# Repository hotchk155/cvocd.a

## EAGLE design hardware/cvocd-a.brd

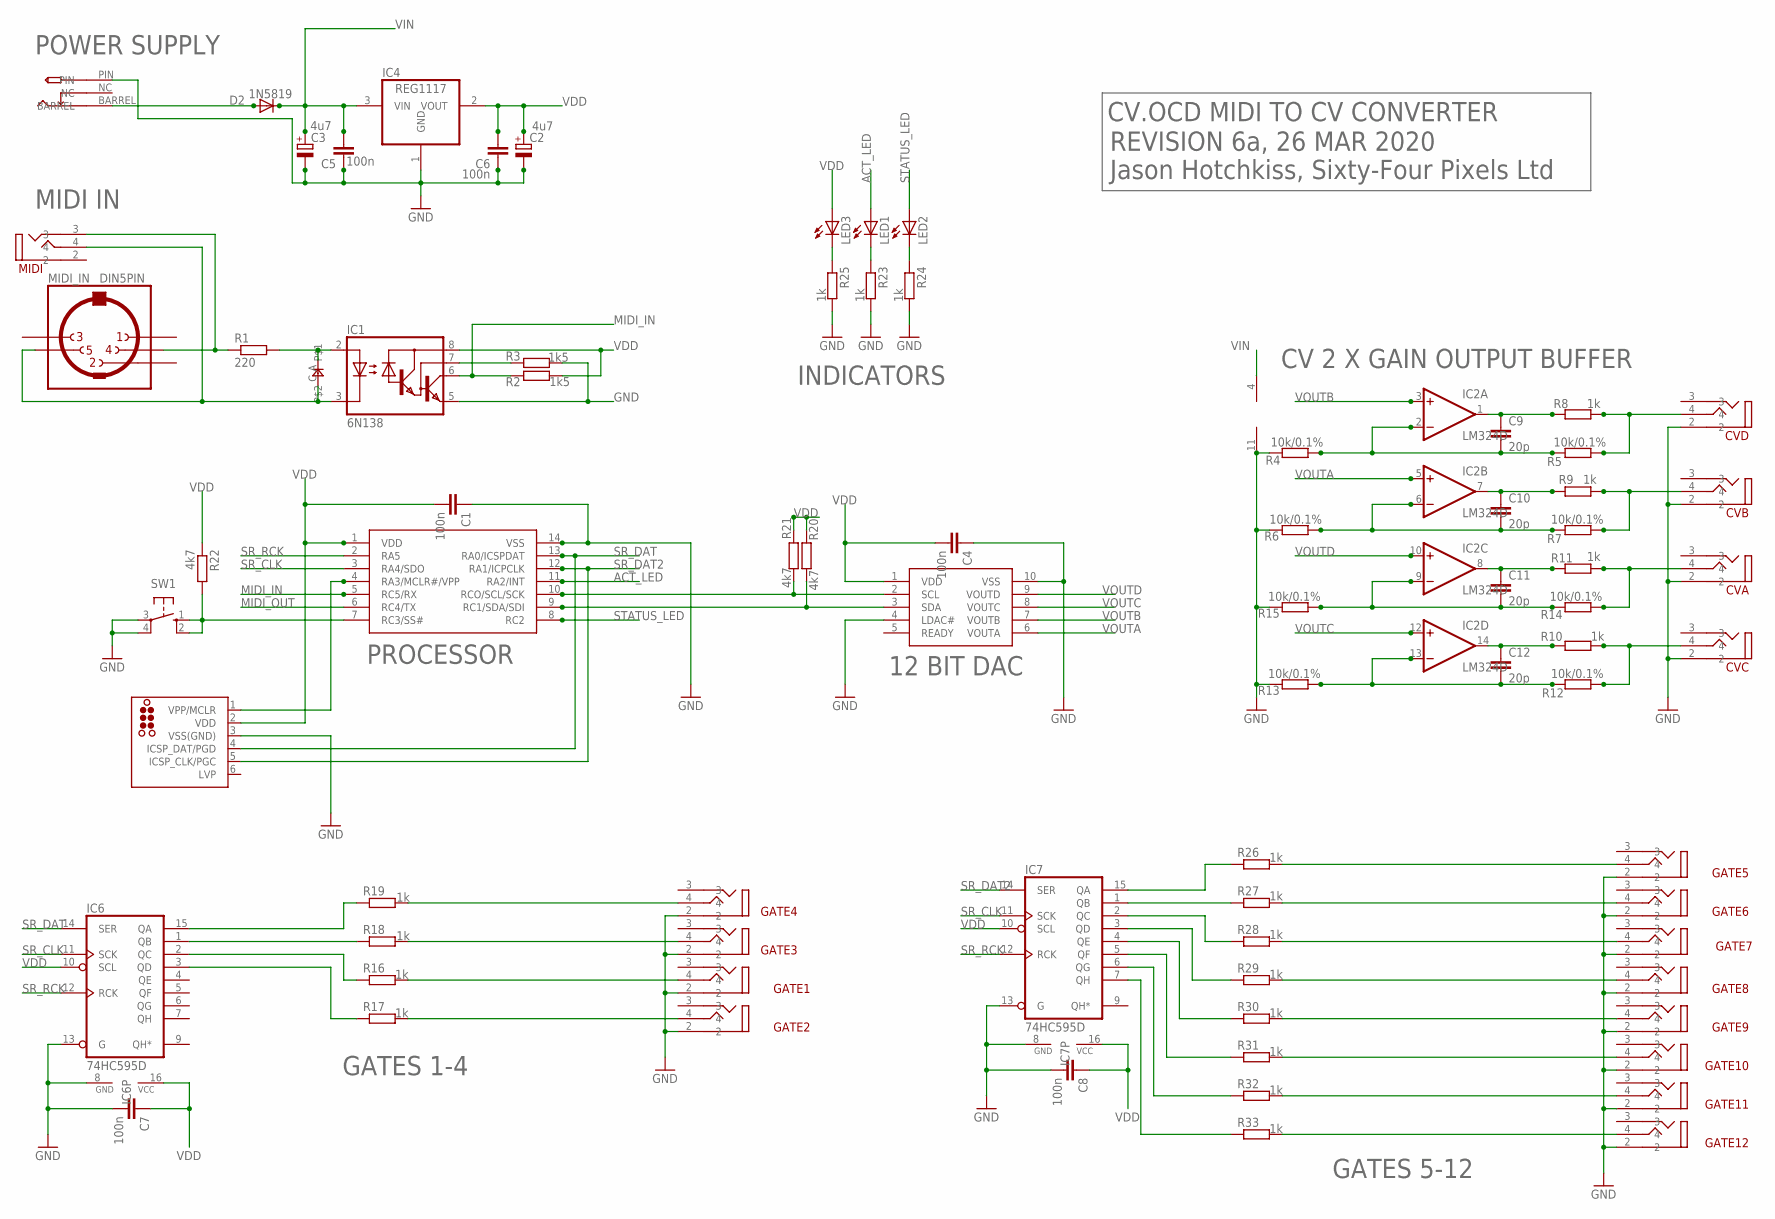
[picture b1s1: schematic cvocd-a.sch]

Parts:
C1, C4, C5, C6, C7, C8: 100n; C0805
C2, C3: 4u7; PANASONIC_C
C9, C10, C11, C12: 20p; C0805
CVA: VERTICAL_3_5MM_SOCKET
CVB: VERTICAL_3_5MM_SOCKET
CVC: VERTICAL_3_5MM_SOCKET
CVD: VERTICAL_3_5MM_SOCKET
D1: 0805DIODE
D2: 1N5819; SOD123
GATE1, GATE2, GATE3, GATE4, GATE5, GATE6, GATE7, GATE8, GATE9, GATE10, GATE11, GATE12: VERTICAL_3_5MM_SOCKET
IC1: 6N138; DIL08
IC2: LM324D; SO14
IC3: MCP4728_QUAD_DAC; MSOP10
IC4: REG1117; SOT223
IC5: PIC16F1825SO14; SO14
IC6, IC7: 74HC595D; SO16
ICSP: TC2030-MCP-NL
LED1, LED2, LED3: LED3MM
MIDI: VERTICAL_3_5MM_SOCKET
MIDI_IN: DIN5PIN; EDGEDIN
R1: 220; R0805
R2, R3: 1k5; R0805
R4, R5, R6, R7, R12, R13, R14, R15: 10k/0.1%; R0805
R8, R9, R10, R11, R16, R17, R18, R19, R23, R24, R25, R26, R27, R28, R29, R30, R31, R32, R33: 1k; R0805
R20, R21, R22: 4k7; R0805
SW1: 10-XX; B3F-10XX
U$2: PWR_SOCKET_2_1MM

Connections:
ACT_LED: IC5.11 (RA2/INT), LED1.A
GND: C1.1, C2.-, C3.-, C4.1, C5.1, C6.1, C7.2, C8.2, CVA.2, CVB.2, CVC.2, CVD.2, GATE1.2, GATE2.2, GATE3.2, GATE4.2, GATE5.2, GATE6.2, GATE7.2, GATE8.2, GATE9.2, GATE10.2, GATE11.2, GATE12.2, IC1.5 (GND), IC2.11 (V-), IC3.4 (LDAC#), IC3.10 (VSS), IC4.1 (GND), IC5.14 (VSS), IC6.8 (GND), IC6.13 (G), IC7.8 (GND), IC7.13 (G), ICSP.3 (VSS(GND)), R3.2, R4.1, R6.1, R13.1, R15.1, R23.2, R24.2, R25.2, SW1.3, SW1.4 (P1), U$2.PIN
MIDI_IN: IC1.6 (VO), IC5.5 (RC5/RX), R2.1
MIDI_OUT: IC5.6 (RC4/TX)
unnamed: GATE4.4, R19.2
unnamed: C9.1, IC2.1 (OUT), R8.1
unnamed: C10.1, IC2.7 (OUT), R9.1
unnamed: C11.1, IC2.8 (OUT), R11.1
unnamed: C12.1, IC2.14 (OUT), R10.1
unnamed: GATE3.4, R18.2
unnamed: GATE1.4, R16.2
unnamed: GATE2.4, R17.2
unnamed: IC5.7 (RC3/SS#), R22.2, SW1.1 (S), SW1.2 (S1)
unnamed: C9.2, IC2.2 (-IN), R4.2, R5.1
unnamed: C11.2, IC2.9 (-IN), R14.1, R15.2
unnamed: IC6.15 (QA), R19.1
unnamed: IC6.1 (QB), R18.1
unnamed: C12.2, IC2.13 (-IN), R12.1, R13.2
unnamed: IC6.3 (QD), R17.1
unnamed: IC6.2 (QC), R16.1
unnamed: CVD.4, R5.2, R8.2
unnamed: CVB.4, R7.2, R9.2
unnamed: GATE5.4, R26.2
unnamed: IC3.2 (SCL), IC5.10 (RCO/SCL/SCK), R21.2
unnamed: IC3.3 (SDA), IC5.9 (RC1/SDA/SDI), R20.2
unnamed: GATE6.4, R27.2
unnamed: GATE7.4, R28.2
unnamed: C10.2, IC2.6 (-IN), R6.2, R7.1
unnamed: MIDI.3, MIDI_IN.4, R1.1
unnamed: D1.A, IC1.2 (A), R1.2
unnamed: D1.C, IC1.3 (C), MIDI.4, MIDI_IN.5
unnamed: GATE8.4, R29.2
unnamed: GATE9.4, R30.2
unnamed: IC5.4 (RA3/MCLR#/VPP), ICSP.1 (VPP/MCLR)
unnamed: LED3.K (C), R25.1
unnamed: LED1.K (C), R23.1
unnamed: LED2.K (C), R24.1
unnamed: CVA.4, R11.2, R14.2
unnamed: GATE10.4, R31.2
unnamed: D2.A, U$2.BARREL
unnamed: GATE11.4, R32.2
unnamed: IC1.7 (VB), R3.1
unnamed: IC7.15 (QA), R26.1
unnamed: CVC.4, R10.2, R12.2
unnamed: IC7.1 (QB), R27.1
unnamed: IC7.3 (QD), R29.1
unnamed: IC7.2 (QC), R28.1
unnamed: IC7.5 (QF), R31.1
unnamed: IC7.6 (QG), R32.1
unnamed: IC7.4 (QE), R30.1
unnamed: GATE12.4, R33.2
unnamed: IC7.7 (QH), R33.1
SR_CLK: IC5.3 (RA4/SDO), IC6.11 (SCK), IC7.11 (SCK)
SR_DAT: IC5.13 (RA0/ICSPDAT), IC6.14 (SER), ICSP.4 (ICSP_DAT/PGD)
SR_DAT2: IC5.12 (RA1/ICPCLK), IC7.14 (SER), ICSP.5 (ICSP_CLK/PGC)
SR_RCK: IC5.2 (RA5), IC6.12 (RCK), IC7.12 (RCK)
STATUS_LED: IC5.8 (RC2), LED2.A
VDD: C1.2, C2.+, C4.2, C6.2, C7.1, C8.1, IC1.8 (VCC), IC3.1 (VDD), IC4.2 (VOUT), IC5.1 (VDD), IC6.10 (SCL), IC6.16 (VCC), IC7.10 (SCL), IC7.16 (VCC), ICSP.2 (VDD), LED3.A, R2.2, R20.1, R21.1, R22.1
VIN: C3.+, C5.2, D2.C, IC2.4 (V+), IC4.3 (VIN)
VOUTA: IC2.5 (+IN), IC3.6 (VOUTA)
VOUTB: IC2.3 (+IN), IC3.7 (VOUTB)
VOUTC: IC2.12 (+IN), IC3.8 (VOUTC)
VOUTD: IC2.10 (+IN), IC3.9 (VOUTD)

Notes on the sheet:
CV.OCD MIDI TO CV CONVERTER
REVISION 6a, 26 MAR 2020
Jason Hotchkiss, Sixty-Four Pixels Ltd
POWER SUPPLY
MIDI IN
PROCESSOR
12 BIT DAC
CV 2 X GAIN OUTPUT BUFFER
GATES 1-4
GATES 5-12
INDICATORS

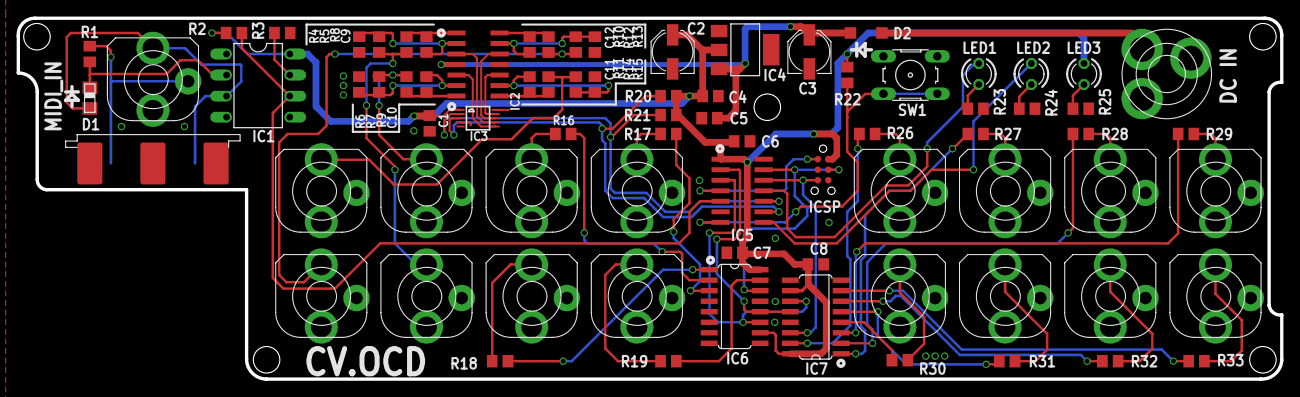
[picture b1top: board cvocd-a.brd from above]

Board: 2 copper layers, 152.5 x 43.6 mm, 78 parts (0 on the bottom side), 62 nets.

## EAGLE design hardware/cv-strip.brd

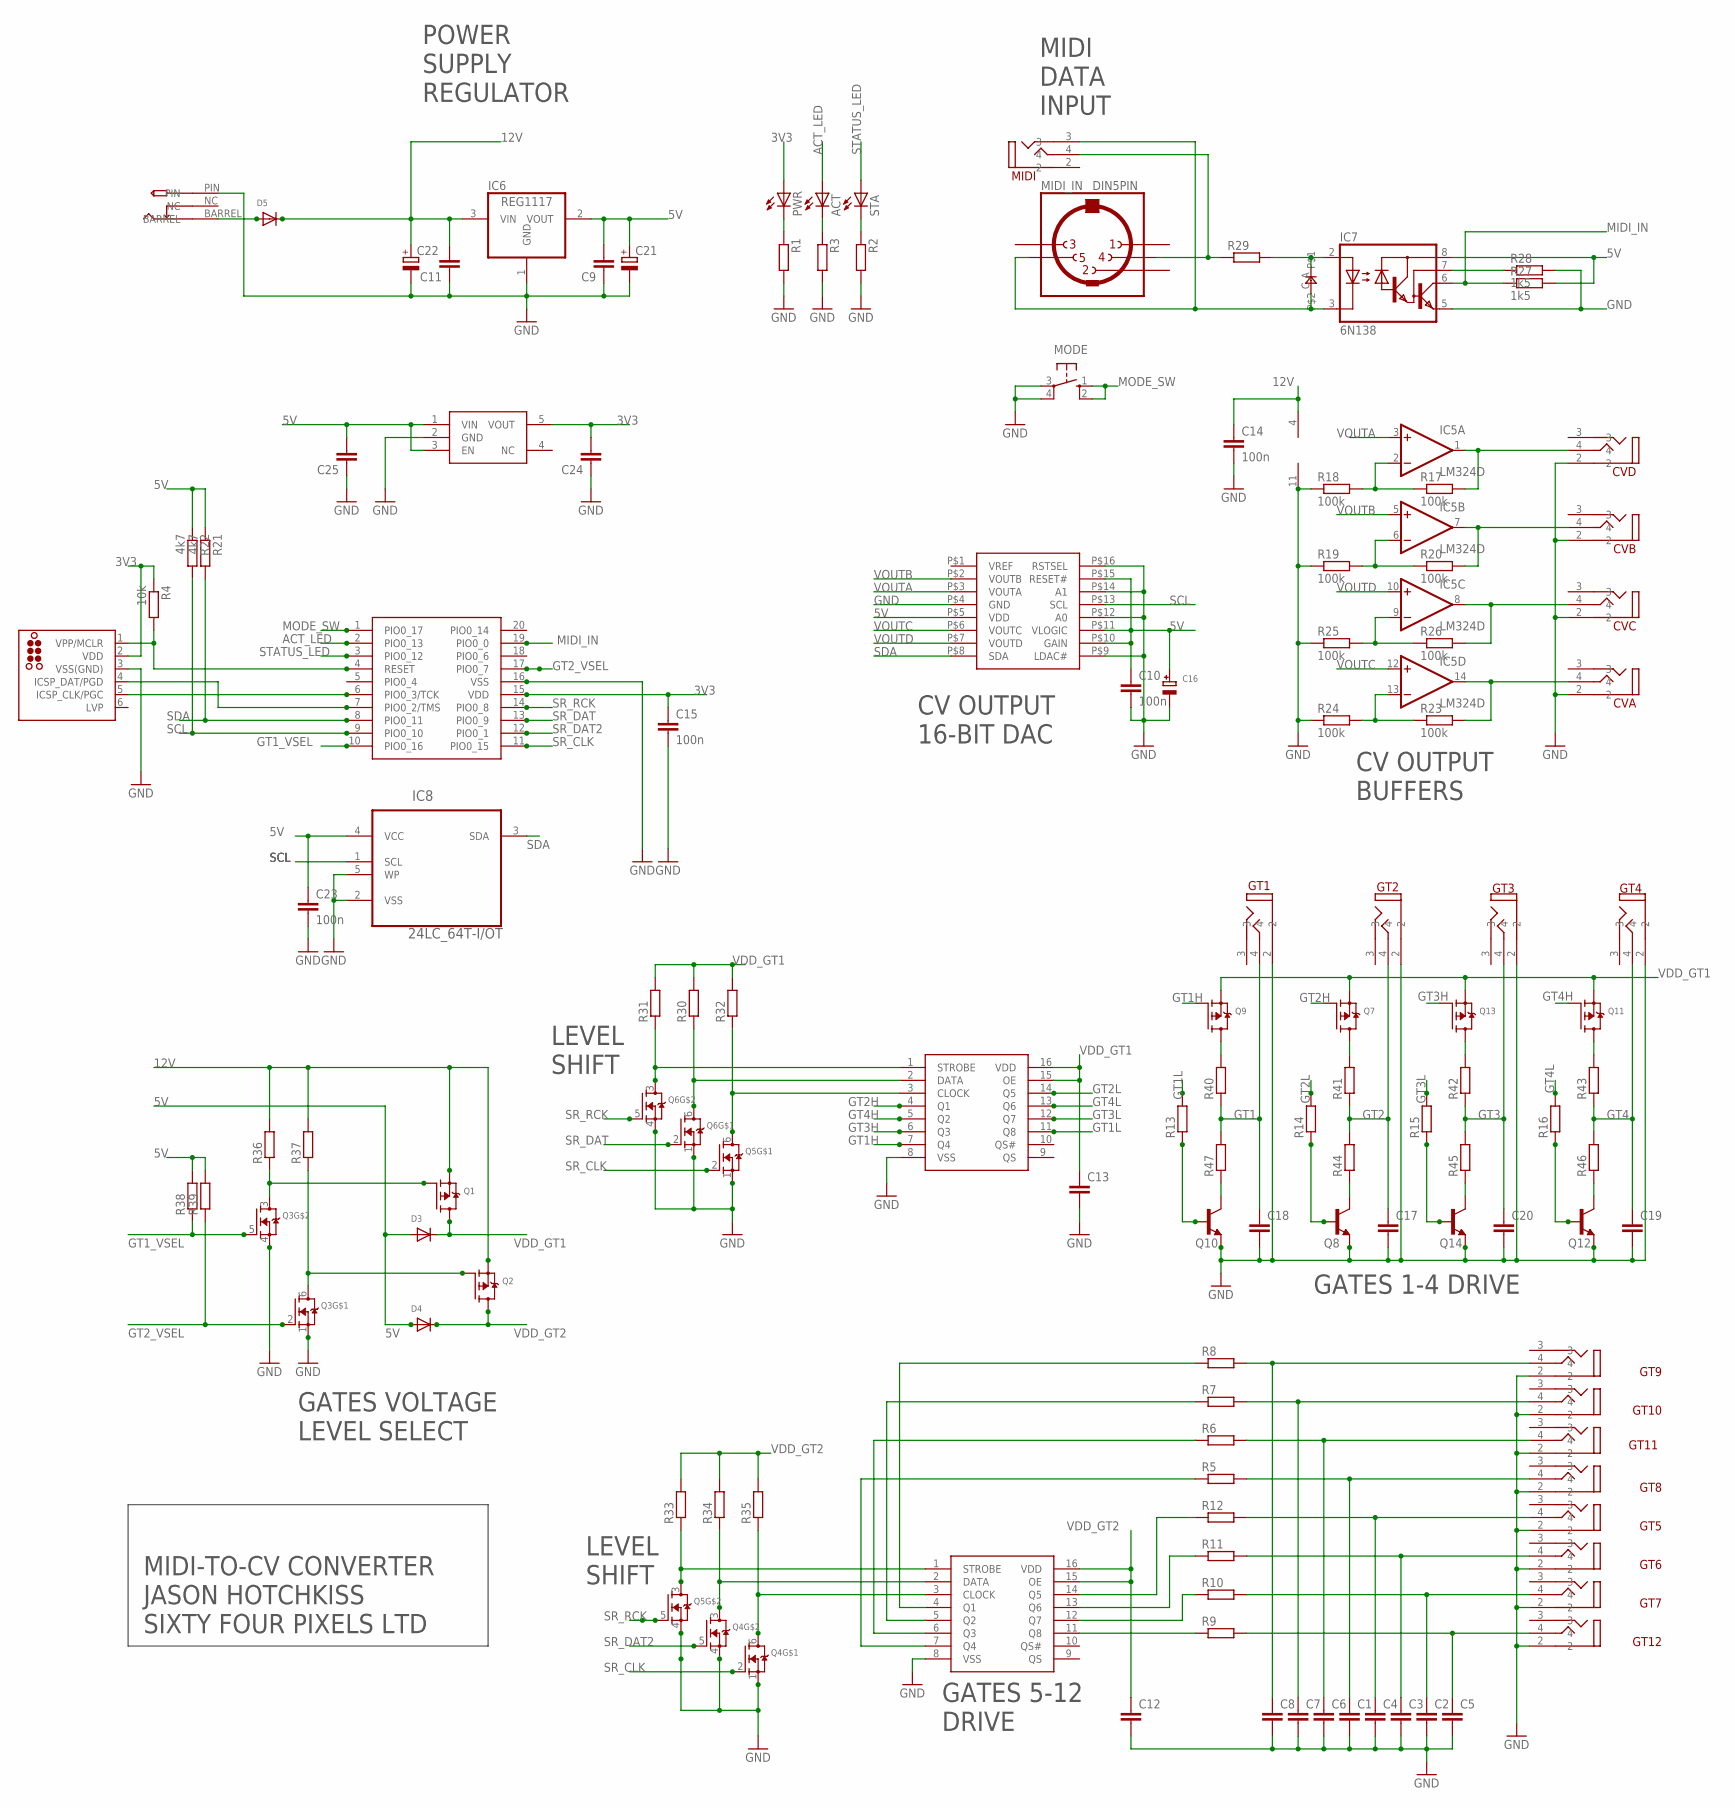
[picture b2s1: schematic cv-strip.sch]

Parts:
ACT: LED3MM
C1, C2, C3, C4, C5, C6, C7, C8, C9, C11, C12, C13, C17, C18, C19, C20, C24, C25: C-EUC0805; C0805
C10, C14, C15, C23: 100n; C0805
C16: CAP_TANTALUMA/3216_REFLOW; EIA3216-18/A-R
C21, C22: CPOL-EUE2.5-5; E2,5-5
CVA: VERTICAL_3_5MM_SOCKET
CVB: VERTICAL_3_5MM_SOCKET
CVC: VERTICAL_3_5MM_SOCKET
CVD: VERTICAL_3_5MM_SOCKET
D1: 0805DIODE
D3, D4, D5: DIODESOD-123; SOD-123
GT1, GT2, GT3, GT4, GT5, GT6, GT7, GT8, GT9, GT10, GT11, GT12: VERTICAL_3_5MM_SOCKET
IC1: LPC812; TSSOP20
IC2: AD5696R; SSOP16
IC3, IC4: MC14094B; SO16
IC5: LM324D; SO14
IC6: REG1117; SOT223
IC7: 6N138; DIL08
IC8: 24LC_64T-I/OT; SOT95P290X145-5N
IC9: MIC5504-2.8YM5-TR; SOT23-5
ICSP: TC2030-MCP-NL
MIDI: VERTICAL_3_5MM_SOCKET
MIDI_IN: DIN5PIN; EDGEDIN
MODE: 10-XX; B3F-10XX
PWR: LED3MM
Q1, Q2, Q7, Q9, Q11, Q13: MOSFET-P; SOT23-R
Q3, Q4, Q5, Q6: MOSFET-N_DUAL; SOT363
Q8, Q10, Q12, Q14: MMBT3904LT1-NPN-SOT23-BEC; SOT23-BEC
R1, R2, R3, R5, R6, R7, R8, R9, R10, R11, R12, R13, R14, R15, R16, R29, R30, R31, R32, R33, R34, R35, R36, R37, R38, R39, R40, R41, R42, R43, R44, R45, R46, R47: R-EU_R0805; R0805
R4: 10k; R0805
R17, R18, R19, R20, R23, R24, R25, R26: 100k; R0805
R21, R22: 4k7; R0805
R27, R28: 1k5; R0805
STA: LED3MM
U$2: PWR_SOCKET_2_1MM

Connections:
3V3: C15.1, C24.2, IC1.15 (VDD), IC9.5 (VOUT), ICSP.2 (VDD), PWR.A, R4.1
5V: C9.2, C10.1, C16.+, C21.+, C23.1, C25.2, D3.A, D4.A, IC2.P$5 (VDD), IC2.P$10 (GAIN), IC2.P$11 (VLOGIC), IC2.P$15 (RESET#), IC6.2 (VOUT), IC7.8 (VCC), IC8.4 (VCC), IC9.1 (VIN), IC9.3 (EN), R21.1, R22.1, R27.2, R38.2, R39.2
12V: C11.2, C14.1, C22.+, D5.C, IC5.4 (V+), IC6.3 (VIN), Q1.2 (S), Q2.2 (S), R36.2, R37.2
ACT_LED: ACT.A, IC1.2 (PIO0_13)
GND: C1.2, C2.2, C3.2, C4.2, C5.2, C6.2, C7.2, C8.2, C9.1, C10.2, C11.1, C12.2, C13.2, C14.2, C15.2, C16.-, C17.2, C18.2, C19.2, C20.2, C21.-, C22.-, C23.2, C24.1, C25.1, CVA.2, CVB.2, CVC.2, CVD.2, GT1.2, GT2.2, GT3.2, GT4.2, GT5.2, GT6.2, GT7.2, GT8.2, GT9.2, GT10.2, GT11.2, GT12.2, IC1.16 (VSS), IC2.P$4 (GND), IC2.P$9 (LDAC#), IC2.P$12 (A0), IC2.P$14 (A1), IC2.P$16 (RSTSEL), IC3.8 (VSS), IC4.8 (VSS), IC5.11 (V-), IC6.1 (GND), IC7.5 (GND), IC8.2 (VSS), IC8.5 (WP), IC9.2 (GND), ICSP.3 (VSS(GND)), MODE.3, MODE.4 (P1), Q3.1 (S), Q3.4 (S), Q4.1 (S), Q4.4 (S), Q5.1 (S), Q5.4 (S), Q6.1 (S), Q6.4 (S), Q8.E, Q10.E, Q12.E, Q14.E, R1.2, R2.2, R3.2, R18.1, R19.1, R24.1, R25.1, R28.2, U$2.PIN
GT1: C18.1, GT1.4, R40.1, R47.2
GT1H: IC3.7 (Q4), Q9.1 (G)
GT1L: IC3.11 (Q8), R13.2
GT1_VSEL: IC1.10 (PIO0_16), Q3.5 (G), R38.1
GT2: C17.1, GT2.4, R41.1, R44.2
GT2H: IC3.4 (Q1), Q7.1 (G)
GT2L: IC3.14 (Q5), R14.2
GT2_VSEL: IC1.17 (PIO0_7), Q3.2 (G), R39.1
GT3: C20.1, GT3.4, R42.1, R45.2
GT3H: IC3.6 (Q3), Q13.1 (G)
GT3L: IC3.12 (Q7), R15.2
GT4: C19.1, GT4.4, R43.1, R46.2
GT4H: IC3.5 (Q2), Q11.1 (G)
GT4L: IC3.13 (Q6), R16.2
MIDI_IN: IC1.19 (PIO0_0), IC7.6 (VO), R27.1
MODE_SW: IC1.1 (PIO0_17), MODE.1 (S), MODE.2 (S1)
unnamed: Q7.3 (D), R41.2
unnamed: CVD.4, IC5.1 (OUT), R17.2
unnamed: CVB.4, IC5.7 (OUT), R20.2
unnamed: CVC.4, IC5.8 (OUT), R26.2
unnamed: CVA.4, IC5.14 (OUT), R23.2
unnamed: Q13.3 (D), R42.2
unnamed: Q11.3 (D), R43.2
unnamed: Q10.B, R13.1
unnamed: Q1.1 (G), Q3.3 (D), R36.1
unnamed: Q8.B, R14.1
unnamed: Q14.B, R15.1
unnamed: Q12.B, R16.1
unnamed: Q8.C, R44.1
unnamed: IC3.1 (STROBE), Q6.3 (D), R31.1
unnamed: IC3.2 (DATA), Q6.6 (D), R30.1
unnamed: IC3.3 (CLOCK), Q5.6 (D), R32.1
unnamed: IC4.11 (Q8), R9.1
unnamed: IC4.12 (Q7), R10.1
unnamed: IC4.13 (Q6), R11.1
unnamed: C8.1, GT9.4, R8.2
unnamed: Q2.1 (G), Q3.6 (D), R37.1
unnamed: C7.1, GT10.4, R7.2
unnamed: C6.1, GT11.4, R6.2
unnamed: IC5.2 (-IN), R17.1, R18.2
unnamed: IC5.6 (-IN), R19.2, R20.1
unnamed: IC5.9 (-IN), R25.2, R26.1
unnamed: IC5.13 (-IN), R23.1, R24.2
unnamed: MIDI.4, MIDI_IN.4, R29.1
unnamed: D1.A, IC7.2 (A), R29.2
unnamed: D1.C, IC7.3 (C), MIDI.3, MIDI_IN.5
unnamed: C1.1, GT8.4, R5.2
unnamed: C4.1, GT5.4, R12.2
unnamed: IC1.6 (PIO0_3/TCK), ICSP.5 (ICSP_CLK/PGC)
unnamed: PWR.K (C), R1.1
unnamed: ACT.K (C), R3.1
unnamed: R2.1, STA.K (C)
unnamed: IC4.14 (Q5), R12.1
unnamed: C3.1, GT6.4, R11.2
unnamed: D5.A, U$2.BARREL
unnamed: C2.1, GT7.4, R10.2
unnamed: IC7.7 (VB), R28.1
unnamed: IC4.7 (Q4), R5.1
unnamed: IC4.6 (Q3), R6.1
unnamed: IC4.5 (Q2), R7.1
unnamed: IC4.4 (Q1), R8.1
unnamed: IC4.1 (STROBE), Q5.3 (D), R33.1
unnamed: IC4.2 (DATA), Q4.3 (D), R34.1
unnamed: IC4.3 (CLOCK), Q4.6 (D), R35.1
unnamed: Q14.C, R45.1
unnamed: C5.1, GT12.4, R9.2
unnamed: Q9.3 (D), R40.2
unnamed: Q12.C, R46.1
unnamed: Q10.C, R47.1
unnamed: IC1.7 (PIO0_2/TMS), ICSP.4 (ICSP_DAT/PGD)
unnamed: IC1.4 (RESET), ICSP.1 (VPP/MCLR), R4.2
SCL: IC1.9 (PIO0_10), IC2.P$13 (SCL), IC8.1 (SCL), R22.2
SDA: IC1.8 (PIO0_11), IC2.P$8 (SDA), IC8.3 (SDA), R21.2
SR_CLK: IC1.11 (PIO0_15), Q4.2 (G), Q5.2 (G)
SR_DAT: IC1.13 (PIO0_9), Q6.2 (G)
SR_DAT2: IC1.12 (PIO0_1), Q4.5 (G)
SR_RCK: IC1.14 (PIO0_8), Q5.5 (G), Q6.5 (G)
STATUS_LED: IC1.3 (PIO0_12), STA.A
VDD_GT1: C13.1, D3.C, IC3.15 (OE), IC3.16 (VDD), Q1.3 (D), Q7.2 (S), Q9.2 (S), Q11.2 (S), Q13.2 (S), R30.2, R31.2, R32.2
VDD_GT2: C12.1, D4.C, IC4.15 (OE), IC4.16 (VDD), Q2.3 (D), R33.2, R34.2, R35.2
VOUTA: IC2.P$3 (VOUTA), IC5.3 (+IN)
VOUTB: IC2.P$2 (VOUTB), IC5.5 (+IN)
VOUTC: IC2.P$6 (VOUTC), IC5.12 (+IN)
VOUTD: IC2.P$7 (VOUTD), IC5.10 (+IN)

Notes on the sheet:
GATES VOLTAGE LEVEL SELECT
CV OUTPUT 16-BIT DAC
CV OUTPUT BUFFERS
GATES 5-12 DRIVE
LEVEL SHIFT
POWER SUPPLY REGULATOR
MIDI DATA INPUT
MIDI-TO-CV CONVERTER JASON HOTCHKISS SIXTY FOUR PIXELS LTD
GATES 1-4 DRIVE

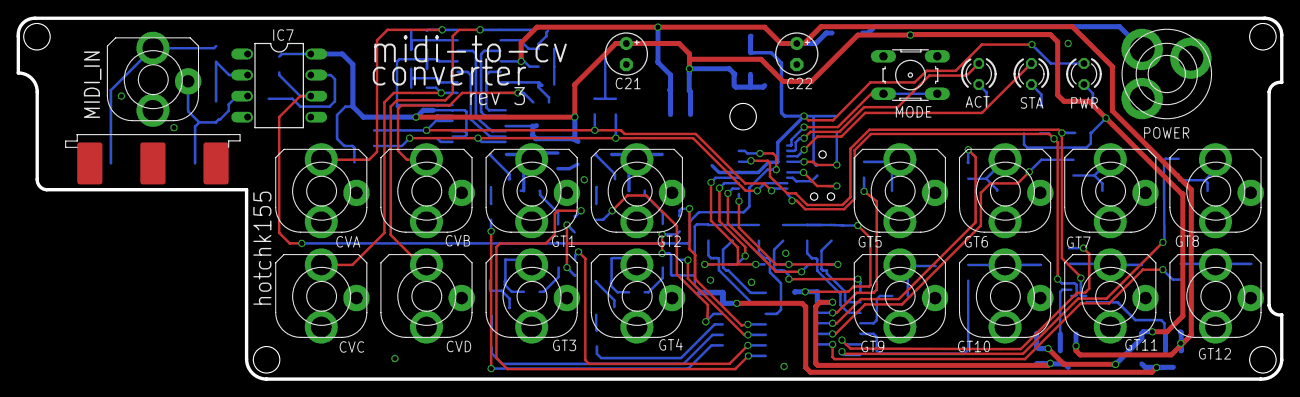
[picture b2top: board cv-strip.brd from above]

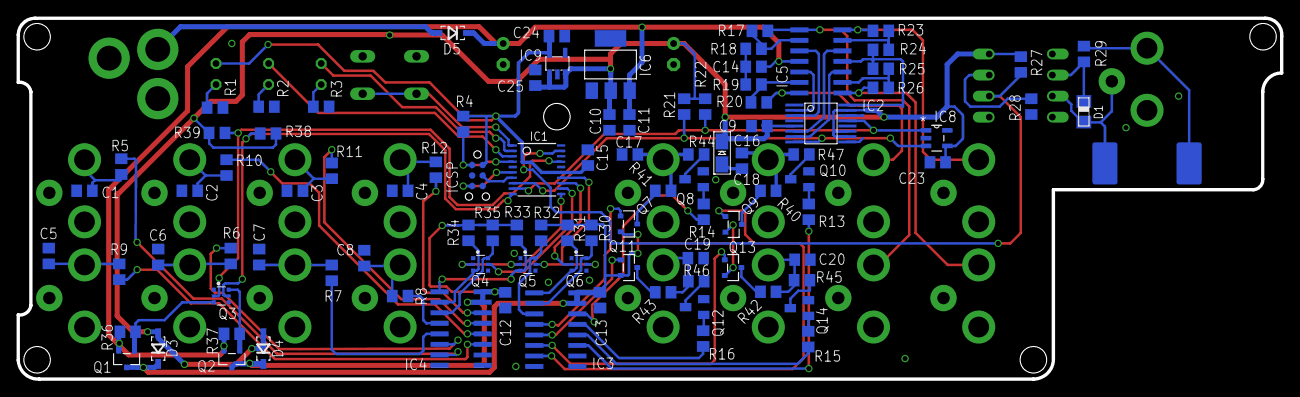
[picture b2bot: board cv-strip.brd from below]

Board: 2 copper layers, 152.5 x 43.6 mm, 123 parts (97 on the bottom side), 89 nets.

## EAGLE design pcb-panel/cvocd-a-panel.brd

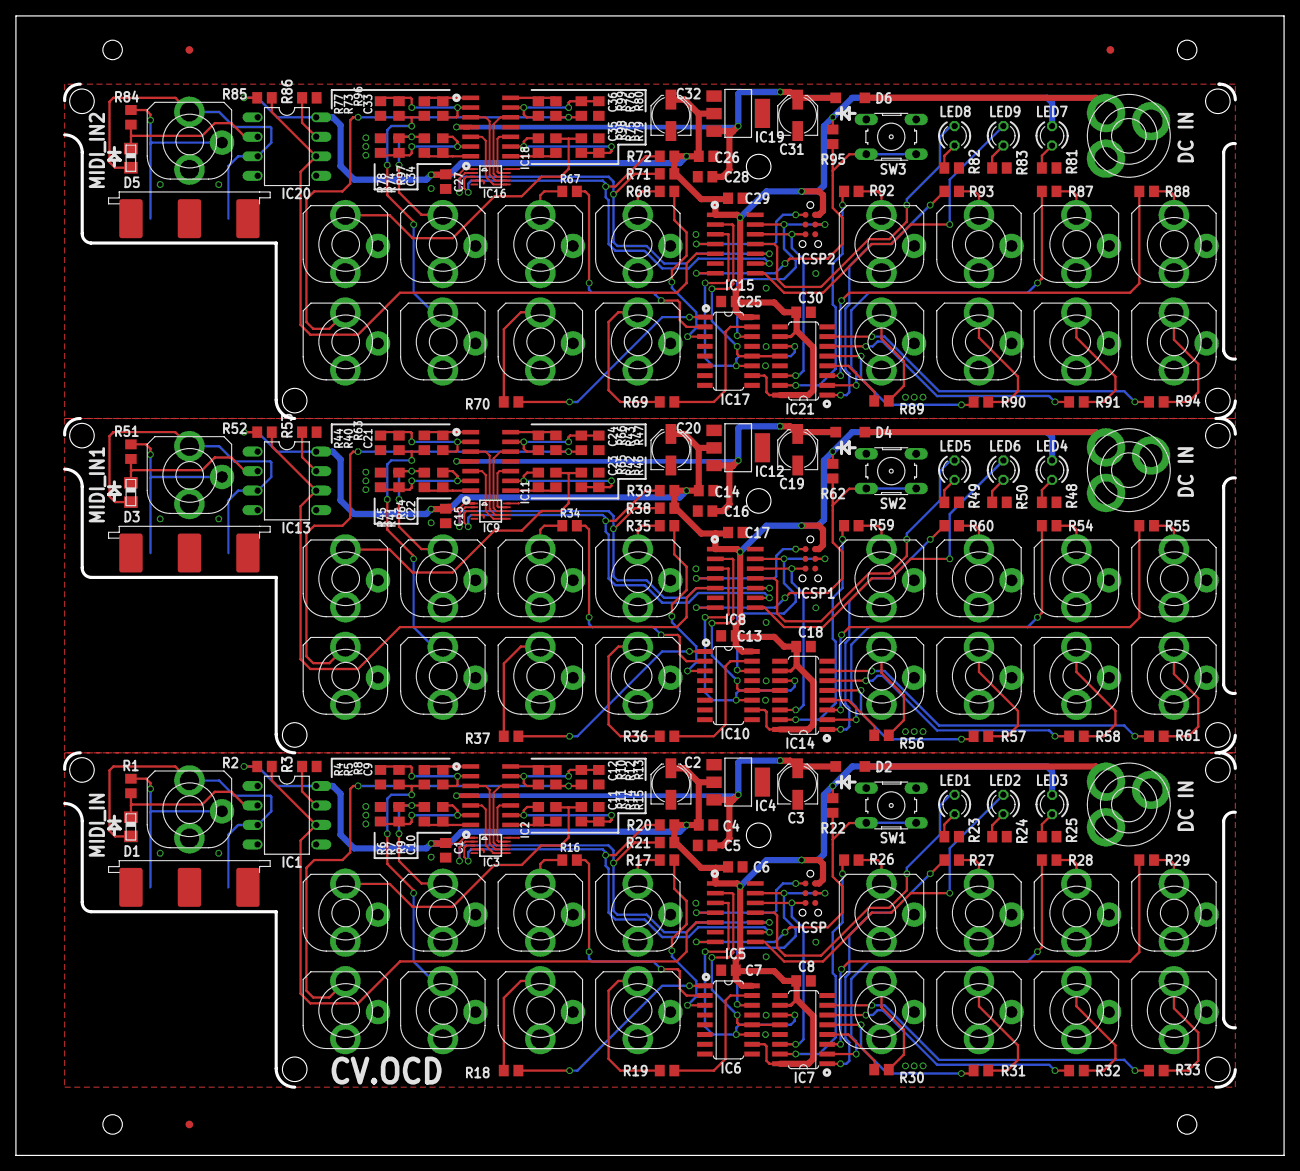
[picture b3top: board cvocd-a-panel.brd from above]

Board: 2 copper layers, 165.0 x 148.2 mm, 237 parts (0 on the bottom side), 186 nets.

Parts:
C1, C4, C5, C6, C7, C8, C13, C14, C15, C16, C17, C18, C25, C26, C27, C28, C29, C30: 100n; C0805
C2, C3, C19, C20, C31, C32: 4u7; PANASONIC_C
C9, C10, C11, C12, C21, C22, C23, C24, C33, C34, C35, C36: 20p; C0805
CVA, CVA1, CVA2: VERTICAL_3_5MM_SOCKET
CVB, CVB1, CVB2: VERTICAL_3_5MM_SOCKET
CVC, CVC1, CVC2: VERTICAL_3_5MM_SOCKET
CVD, CVD1, CVD2: VERTICAL_3_5MM_SOCKET
D1, D3, D5: 0805DIODE
D2, D4, D6: 1N5819; SOD123
E$1, E$2, E$3: FIDUCIAL_1MM
GATE1, GATE2, GATE3, GATE4, GATE5, GATE6, GATE7, GATE8, GATE9, GATE10, GATE11, GATE12, GATE13, GATE14, GATE15, GATE16, GATE17, GATE18, GATE19, GATE20, GATE21, GATE22, GATE23, GATE24, GATE25, GATE26, GATE27, GATE28, GATE29, GATE30, GATE31, GATE32, GATE33, GATE34, GATE35, GATE36: VERTICAL_3_5MM_SOCKET
IC1, IC13, IC20: 6N138; DIL08
IC2, IC11, IC18: LM324D; SO14
IC3, IC9, IC16: MCP4728_QUAD_DAC; MSOP10
IC4, IC12, IC19: REG1117; SOT223
IC5, IC8, IC15: PIC16F1825SO14; SO14
IC6, IC7, IC10, IC14, IC17, IC21: 74HC595D; SO16
ICSP, ICSP1, ICSP2: TC2030-MCP-NL
LED1, LED2, LED3, LED4, LED5, LED6, LED7, LED8, LED9: LED3MM
MIDI, MIDI1, MIDI2: VERTICAL_3_5MM_SOCKET
MIDI_IN, MIDI_IN1, MIDI_IN2: DIN5PIN; EDGEDIN
R1, R51, R84: 220; R0805
R2, R3, R52, R53, R85, R86: 1k5; R0805
R4, R5, R6, R7, R12, R13, R14, R15, R40, R41, R42, R43, R44, R45, R46, R47, R73, R74, R75, R76, R77, R78, R79, R80: 10k/0.1%; R0805
R8, R9, R10, R11, R16, R17, R18, R19, R23, R24, R25, R26, R27, R28, R29, R30, R31, R32, R33, R34, R35, R36, R37, R48, R49, R50, R54, R55, R56, R57, R58, R59, R60, R61, R63, R64, R65, R66, R67, R68, R69, R70, R81, R82, R83, R87, R88, R89, R90, R91, R92, R93, R94, R96, R97, R98, R99: 1k; R0805
R20, R21, R22, R38, R39, R62, R71, R72, R95: 4k7; R0805
SW1, SW2, SW3: B3F-10XX
U$1, U$2, U$3: PWR_SOCKET_2_1MM

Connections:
ACT_LED: IC5.11, LED1.A
ACT_LED1: IC8.11, LED5.A
ACT_LED2: IC15.11, LED8.A
GND: C1.1, C2.-, C3.-, C4.1, C5.1, C6.1, C7.2, C8.2, CVA.2, CVB.2, CVC.2, CVD.2, GATE1.2, GATE2.2, GATE3.2, GATE4.2, GATE5.2, GATE6.2, GATE7.2, GATE8.2, GATE9.2, GATE10.2, GATE11.2, GATE12.2, IC1.5, IC2.11, IC3.4, IC3.10, IC4.1, IC5.14, IC6.8, IC6.13, IC7.8, IC7.13, ICSP.3, R3.2, R4.1, R6.1, R13.1, R15.1, R23.2, R24.2, R25.2, SW1.3, SW1.4, U$2.PIN
GND1: C13.2, C14.1, C15.1, C16.1, C17.1, C18.2, C19.-, C20.-, CVA1.2, CVB1.2, CVC1.2, CVD1.2, GATE13.2, GATE14.2, GATE15.2, GATE16.2, GATE17.2, GATE18.2, GATE19.2, GATE20.2, GATE21.2, GATE22.2, GATE23.2, GATE24.2, IC8.14, IC9.4, IC9.10, IC10.8, IC10.13, IC11.11, IC12.1, IC13.5, IC14.8, IC14.13, ICSP1.3, R44.1, R45.1, R46.1, R47.1, R48.2, R49.2, R50.2, R53.2, SW2.3, SW2.4, U$1.PIN
GND2: C25.2, C26.1, C27.1, C28.1, C29.1, C30.2, C31.-, C32.-, CVA2.2, CVB2.2, CVC2.2, CVD2.2, GATE25.2, GATE26.2, GATE27.2, GATE28.2, GATE29.2, GATE30.2, GATE31.2, GATE32.2, GATE33.2, GATE34.2, GATE35.2, GATE36.2, IC15.14, IC16.4, IC16.10, IC17.8, IC17.13, IC18.11, IC19.1, IC20.5, IC21.8, IC21.13, ICSP2.3, R77.1, R78.1, R79.1, R80.1, R81.2, R82.2, R83.2, R86.2, SW3.3, SW3.4, U$3.PIN
MIDI_IN: IC1.6, IC5.5, R2.1
MIDI_IN1: IC8.5, IC13.6, R52.1
MIDI_IN2: IC15.5, IC20.6, R85.1
unnamed: GATE4.4, R19.2
unnamed: C9.1, IC2.1, R8.1
unnamed: C10.1, IC2.7, R9.1
unnamed: C11.1, IC2.8, R11.1
unnamed: C12.1, IC2.14, R10.1
unnamed: GATE3.4, R18.2
unnamed: GATE1.4, R16.2
unnamed: GATE2.4, R17.2
unnamed: IC5.7, R22.2, SW1.1, SW1.2
unnamed: C9.2, IC2.2, R4.2, R5.1
unnamed: C11.2, IC2.9, R14.1, R15.2
unnamed: IC6.15, R19.1
unnamed: IC6.1, R18.1
unnamed: C12.2, IC2.13, R12.1, R13.2
unnamed: IC6.3, R17.1
unnamed: IC6.2, R16.1
unnamed: GATE13.4, R36.2
unnamed: CVD.4, R5.2, R8.2
unnamed: CVB.4, R7.2, R9.2
unnamed: GATE5.4, R26.2
unnamed: IC3.2, IC5.10, R21.2
unnamed: IC3.3, IC5.9, R20.2
unnamed: GATE6.4, R27.2
unnamed: GATE7.4, R28.2
unnamed: GATE14.4, R37.2
unnamed: C10.2, IC2.6, R6.2, R7.1
unnamed: GATE15.4, R34.2
unnamed: GATE16.4, R35.2
unnamed: MIDI.3, MIDI_IN.4, R1.1
unnamed: D1.A, IC1.2, R1.2
unnamed: D1.C, IC1.3, MIDI.4, MIDI_IN.5
unnamed: GATE8.4, R29.2
unnamed: GATE9.4, R30.2
unnamed: IC5.4, ICSP.1
unnamed: LED3.K, R25.1
unnamed: LED1.K, R23.1
unnamed: LED2.K, R24.1
unnamed: CVA.4, R11.2, R14.2
unnamed: GATE10.4, R31.2
unnamed: D2.A, U$2.BARREL
unnamed: GATE11.4, R32.2
unnamed: IC1.7, R3.1
unnamed: IC7.15, R26.1
unnamed: CVC.4, R10.2, R12.2
unnamed: IC10.15, R36.1
unnamed: IC7.1, R27.1
unnamed: IC7.3, R29.1
unnamed: IC7.2, R28.1
unnamed: IC7.5, R31.1
unnamed: IC7.6, R32.1
unnamed: IC7.4, R30.1
unnamed: GATE12.4, R33.2
unnamed: IC7.7, R33.1
unnamed: IC10.1, R37.1
unnamed: IC10.3, R35.1
unnamed: IC10.2, R34.1
unnamed: IC8.10, IC9.2, R38.2
unnamed: IC8.9, IC9.3, R39.2
unnamed: C21.1, IC11.1, R63.1
unnamed: C22.1, IC11.7, R64.1
unnamed: C23.1, IC11.8, R65.1
unnamed: C24.1, IC11.14, R66.1
unnamed: C22.2, IC11.6, R41.1, R45.2
unnamed: IC8.4, ICSP1.1
unnamed: LED4.K, R48.1
unnamed: LED5.K, R49.1
unnamed: LED6.K, R50.1
unnamed: D4.A, U$1.BARREL
unnamed: MIDI1.3, MIDI_IN1.4, R51.1
unnamed: D3.A, IC13.2, R51.2
unnamed: D3.C, IC13.3, MIDI1.4, MIDI_IN1.5
unnamed: IC13.7, R53.1
unnamed: GATE17.4, R59.2
unnamed: GATE18.4, R60.2
unnamed: GATE19.4, R54.2
unnamed: GATE20.4, R55.2
unnamed: GATE21.4, R56.2
unnamed: GATE22.4, R57.2
unnamed: GATE23.4, R58.2
unnamed: IC14.15, R59.1
unnamed: IC14.1, R60.1
unnamed: IC14.3, R55.1
unnamed: IC14.2, R54.1
unnamed: IC14.5, R57.1
unnamed: IC14.6, R58.1
unnamed: IC14.4, R56.1
unnamed: GATE24.4, R61.2
unnamed: IC14.7, R61.1
unnamed: IC8.7, R62.2, SW2.1, SW2.2
unnamed: CVD1.4, R40.2, R63.2
unnamed: CVB1.4, R41.2, R64.2
unnamed: CVA1.4, R42.2, R65.2
unnamed: CVC1.4, R43.2, R66.2
unnamed: C21.2, IC11.2, R40.1, R44.2
unnamed: C23.2, IC11.9, R42.1, R46.2
unnamed: C24.2, IC11.13, R43.1, R47.2
unnamed: GATE25.4, R69.2
unnamed: GATE26.4, R70.2
unnamed: GATE27.4, R67.2
unnamed: GATE28.4, R68.2
unnamed: IC17.15, R69.1
unnamed: IC17.1, R70.1
unnamed: IC17.3, R68.1
unnamed: IC17.2, R67.1
unnamed: IC15.10, IC16.2, R71.2
unnamed: IC15.9, IC16.3, R72.2
unnamed: C33.1, IC18.1, R96.1
unnamed: C34.1, IC18.7, R97.1
unnamed: C35.1, IC18.8, R98.1
unnamed: C36.1, IC18.14, R99.1
unnamed: C34.2, IC18.6, R74.1, R78.2
unnamed: IC15.4, ICSP2.1
unnamed: LED7.K, R81.1
unnamed: LED8.K, R82.1
unnamed: LED9.K, R83.1
unnamed: D6.A, U$3.BARREL
unnamed: MIDI2.3, MIDI_IN2.4, R84.1
unnamed: D5.A, IC20.2, R84.2
unnamed: D5.C, IC20.3, MIDI2.4, MIDI_IN2.5
unnamed: IC20.7, R86.1
unnamed: GATE29.4, R92.2
unnamed: GATE30.4, R93.2
unnamed: GATE31.4, R87.2
unnamed: GATE32.4, R88.2
unnamed: GATE33.4, R89.2
unnamed: GATE34.4, R90.2
unnamed: GATE35.4, R91.2
unnamed: IC21.15, R92.1
unnamed: IC21.1, R93.1
unnamed: IC21.3, R88.1
unnamed: IC21.2, R87.1
unnamed: IC21.5, R90.1
unnamed: IC21.6, R91.1
unnamed: IC21.4, R89.1
unnamed: GATE36.4, R94.2
unnamed: IC21.7, R94.1
unnamed: IC15.7, R95.2, SW3.1, SW3.2
unnamed: CVD2.4, R73.2, R96.2
unnamed: CVB2.4, R74.2, R97.2
unnamed: CVA2.4, R75.2, R98.2
unnamed: CVC2.4, R76.2, R99.2
unnamed: C33.2, IC18.2, R73.1, R77.2
unnamed: C35.2, IC18.9, R75.1, R79.2
unnamed: C36.2, IC18.13, R76.1, R80.2
SR_CLK: IC5.3, IC6.11, IC7.11
SR_CLK1: IC8.3, IC10.11, IC14.11
SR_CLK2: IC15.3, IC17.11, IC21.11
SR_DAT: IC5.13, IC6.14, ICSP.4
SR_DAT1: IC8.13, IC10.14, ICSP1.4
SR_DAT2: IC5.12, IC7.14, ICSP.5
SR_DAT3: IC8.12, IC14.14, ICSP1.5
SR_DAT4: IC15.13, IC17.14, ICSP2.4
SR_DAT5: IC15.12, IC21.14, ICSP2.5
SR_RCK: IC5.2, IC6.12, IC7.12
SR_RCK1: IC8.2, IC10.12, IC14.12
SR_RCK2: IC15.2, IC17.12, IC21.12
STATUS_LED: IC5.8, LED2.A
STATUS_LED1: IC8.8, LED6.A
STATUS_LED2: IC15.8, LED9.A
VDD: C1.2, C2.+, C4.2, C6.2, C7.1, C8.1, IC1.8, IC3.1, IC4.2, IC5.1, IC6.10, IC6.16, IC7.10, IC7.16, ICSP.2, LED3.A, R2.2, R20.1, R21.1, R22.1
VDD1: C13.1, C14.2, C15.2, C17.2, C18.1, C20.+, IC8.1, IC9.1, IC10.10, IC10.16, IC12.2, IC13.8, IC14.10, IC14.16, ICSP1.2, LED4.A, R38.1, R39.1, R52.2, R62.1
VDD2: C25.1, C26.2, C27.2, C29.2, C30.1, C32.+, IC15.1, IC16.1, IC17.10, IC17.16, IC19.2, IC20.8, IC21.10, IC21.16, ICSP2.2, LED7.A, R71.1, R72.1, R85.2, R95.1
VIN: C3.+, C5.2, D2.C, IC2.4, IC4.3
VIN1: C16.2, C19.+, D4.C, IC11.4, IC12.3
VIN2: C28.2, C31.+, D6.C, IC18.4, IC19.3
VOUTA: IC2.5, IC3.6
VOUTA1: IC9.6, IC11.5
VOUTA2: IC16.6, IC18.5
VOUTB: IC2.3, IC3.7
VOUTB1: IC9.7, IC11.3
VOUTB2: IC16.7, IC18.3
VOUTC: IC2.12, IC3.8
VOUTC1: IC9.8, IC11.12
VOUTC2: IC16.8, IC18.12
VOUTD: IC2.10, IC3.9
VOUTD1: IC9.9, IC11.10
VOUTD2: IC16.9, IC18.10

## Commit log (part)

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2016-02-05 :circus_tent: Added .gitattributes & .gitignore files
2016-02-11 getting there
2016-02-11 almost done?
2016-02-11 tweaks
2016-03-05 pcb v1
2016-03-23 initial version
2016-03-23 add comp values
2016-03-25 firmware
2016-03-26 working on it
2016-04-03 in progress
2016-04-09 stuff
2016-05-07 test release 0.1
2016-05-09 rev0.2
2016-05-23 fixes
    fix pitch bend, reset cv to zero
2016-05-23 retrigs, pitch bend cv, fixes
2016-05-24 auto save, bpm to cv, cc to cv
2016-05-24 test voltage, clock
2016-05-24 rev0.3
2016-05-26 bit of tidying up
2016-05-29 rev2 updates - checking needed
2016-06-10 extra n fet on voltage select circuits
2016-06-13 PCBrev2
2016-06-13 Final rev 2 release PCB
2016-06-14 REV2A
    fixed some DRC issues
2016-07-08 updates for new shift reg
2016-07-08 16bit dac changes
2016-07-09 cv mods
2016-07-16 working on rev 3 LPC812
2016-07-18 mods
2016-07-18 rev3 PCB final
2016-07-23 label changes only
2016-08-12 Reverting master back to original PIC code for 12bit DAC
2016-08-24 working on CV gate mode
2016-08-24 rename
2016-09-26 Revert "working on CV gate mode"
    This reverts commit b332149b2ce033c2ec8ef14785a9b57907feba7d.
2016-09-26 test program updated
2016-09-26 1.0 release candidate
2016-10-14 various mods and fixes
2016-10-14 remove split message for now
2016-10-14 fixes from tests
2016-10-14 Slot stealing in chord mode
2016-10-17 user guide
2016-10-17 docs
2016-10-17 note range
2016-10-24 packing slip
2016-10-24 Revert "packing slip"
    This reverts commit 48e4d3a89401627845a863b18054c9caac200d1a.
2016-11-10 reorg
2016-11-11 Hz/Volt
2016-11-11 1.1beta
2017-01-30 transport toggle mode
2017-02-12 1.3beta
    fix to CC channel handling
2017-04-03 rev2
2017-05-20 rev2.1 Fix issue with negative transpose amounts
2017-05-20 rev2.2 1.2V/oct
2017-10-01 2.2BETA -> REV3
2017-10-01 rename 3->3.0
2017-10-14 rebuild after config page fix
2017-10-14 rebuild with new web page
2017-12-09 smts moved to top of board
2017-12-10 pcb bitmap
2017-12-10 license logo
2017-12-10 tidy up silk
2017-12-30 icsp to top layer, current lim resistors
2018-01-02 adding teensy test rig sketch
2018-01-03 3.1 beta - add calibration features / temp remove BPM->CV
2018-01-03 keep __f file!
2018-01-03 3.1beta
2018-01-03 hshs
2018-01-22 V3 possible final..
2018-01-23 Revert "aaa"
    This reverts commit 3954c3311754772a76ec03b990afd23774723b60.
2018-01-28 working on v4
2018-01-30 REV4 RELEASE CANDIDATE
2018-02-19 v5 board first version
2018-02-22 v5 pcb release candidate
2018-03-12 V5.1 SILK SCREEN UPDATES
2018-05-12 rev4.0
2018-05-24 Fix issue with skipping system common messages with parameters
2018-06-11 mtc fix
2018-07-04 triangle waves
2018-07-13 following fix to web page
2018-07-19 before new board
2018-07-21 backup
2018-07-21 more updates
2018-07-22 work
2018-07-22 old version
2018-07-22 final tweaks
2018-09-10 rev 4.1 beta
    correct an issue where midi note gates could trigger on any note when on same midi channel as a note input
2018-09-10 add 4.1 and 4.2 to archive folder
2018-09-10 no change
2018-12-15 midi spec added
2018-12-22 config page
2018-12-23 ssss
2018-12-27 dsfs
2018-12-27 cvocfg
2019-01-06 gfdg
2019-01-24 4.2beta->5 release
2019-01-24 label
2019-02-25 5.1BETA
    Improvement to monophonic note modes to allow paraphonic operation. Fix stuck note gate issue due to deferred gate on events
2019-04-23 add config spec
2019-06-18 paraphonic chord note added
2019-06-18 5.2 beta
2020-01-17 V6 candidate
    change polarity on mini midi in socket
2020-03-26 REV 6A - Diode direction marking only
2020-04-28 gate 12 description
2020-06-28 PCB front panel
2020-06-28 move config page
2020-07-07 Bump electron from 4.0.0 to 7.2.4 in /cvocfg
    Bumps [electron](https://github.com/electron/electron) from 4.0.0 to 7.2.4.
    - [Release notes](https://github.com/electron/electron/releases)
    - [Changelog](https://github.com/electron/electron/blob/master/docs/breaking-changes.md)
    - [Commits](https://github.com/electron/electron/compare/v4.0.0...v7.2.4)
2021-01-26 TRS MMA
2021-01-28 Bump electron from 4.0.0 to 9.4.0 in /cvocfg
    Bumps [electron](https://github.com/electron/electron) from 4.0.0 to 9.4.0.
    - [Release notes](https://github.com/electron/electron/releases)
    - [Changelog](https://github.com/electron/electron/blob/master/docs/breaking-changes.md)
    - [Commits](https://github.com/electron/electron/compare/v4.0.0...v9.4.0)
2021-10-12 Bump electron from 4.0.0 to 11.5.0 in /cvocfg
    Bumps [electron](https://github.com/electron/electron) from 4.0.0 to 11.5.0.
    - [Release notes](https://github.com/electron/electron/releases)
    - [Changelog](https://github.com/electron/electron/blob/main/docs/breaking-changes.md)
    - [Commits](https://github.com/electron/electron/compare/v4.0.0...v11.5.0)
    ---
    updated-dependencies:
2022-03-25 Bump electron from 4.0.0 to 13.6.6 in /cvocfg
    Bumps [electron](https://github.com/electron/electron) from 4.0.0 to 13.6.6.
    - [Release notes](https://github.com/electron/electron/releases)
    - [Changelog](https://github.com/electron/electron/blob/main/docs/breaking-changes.md)
    - [Commits](https://github.com/electron/electron/compare/v4.0.0...v13.6.6)
    ---
    updated-dependencies:
2022-06-13 test rig change
2022-06-16 Bump electron from 4.0.0 to 15.5.5 in /cvocfg
    Bumps [electron](https://github.com/electron/electron) from 4.0.0 to 15.5.5.
    - [Release notes](https://github.com/electron/electron/releases)
    - [Changelog](https://github.com/electron/electron/blob/main/docs/breaking-changes.md)
    - [Commits](https://github.com/electron/electron/compare/v4.0.0...v15.5.5)
    ---
    updated-dependencies:
2022-07-27 A6 test firmware
2022-07-27 add source images
2022-08-29 add async sending to cal tool
2022-11-02 add A0 to archive
2022-11-10 Bump electron from 4.0.0 to 18.3.7 in /cvocfg
    Bumps [electron](https://github.com/electron/electron) from 4.0.0 to 18.3.7.
    - [Release notes](https://github.com/electron/electron/releases)
    - [Changelog](https://github.com/electron/electron/blob/main/docs/breaking-changes.md)
    - [Commits](https://github.com/electron/electron/compare/v4.0.0...v18.3.7)
    ---
    updated-dependencies:
2022-11-27 initial experimental build with MPLAB.X
2023-02-28 Bump minimist and extract-zip in /cvocfg
    Bumps [minimist](https://github.com/minimistjs/minimist) and [extract-zip](https://github.com/maxogden/extract-zip). These dependencies needed to be updated together.
    Updates `minimist` from 1.2.0 to 1.2.8
    - [Release notes](https://github.com/minimistjs/minimist/releases)
    - [Changelog](https://github.com/minimistjs/minimist/blob/main/CHANGELOG.md)
    - [Commits](https://github.com/minimistjs/minimist/compare/v1.2.0...v1.2.8)
    Updates `extract-zip` from 1.6.7 to 1.7.0
2023-04-17 Bump json-schema and jsprim in /cvocfg
    Bumps [json-schema](https://github.com/kriszyp/json-schema) and [jsprim](https://github.com/joyent/node-jsprim). These dependencies needed to be updated together.
    Updates `json-schema` from 0.2.3 to 0.4.0
    - [Release notes](https://github.com/kriszyp/json-schema/releases)
    - [Commits](https://github.com/kriszyp/json-schema/compare/v0.2.3...v0.4.0)
    Updates `jsprim` from 1.4.1 to 1.4.2
    - [Release notes](https://github.com/joyent/node-jsprim/releases)
2023-04-17 Bump ajv from 6.6.2 to 6.12.6 in /cvocfg
    Bumps [ajv](https://github.com/ajv-validator/ajv) from 6.6.2 to 6.12.6.
    - [Release notes](https://github.com/ajv-validator/ajv/releases)
    - [Commits](https://github.com/ajv-validator/ajv/compare/v6.6.2...v6.12.6)
    ---
    updated-dependencies:
    - dependency-name: ajv
2025-04-09 test firmware update
2026-02-02 add manual images
2026-02-02 chord mode changes in progress
2026-02-03 changes to chord modes
2026-02-03 chord mode updates
2026-02-04 chord mode changes complete and tested
2026-02-06 chord mode changes following hardware tests
2026-02-06 add 5.2 and 5.3 SYSEX files to release folders
2026-02-06 update to midi spec
2026-02-06 updates to UI for rev 5.3
2026-02-11 manual update 5.3
2026-02-11 initial XC8 for vscode build
2026-02-11 xc8 updates
2026-02-13 slew/glide/bpmtocv
2026-02-26 remove old MPLABX project
2026-03-26 banana board in progress
2026-03-26 REV1
2026-03-27 updates to banana pcb
2026-03-27 fascia
2026-03-28 pcb and fascia version 1
2026-04-17 additional mounting holes on fascia
2026-04-21 banana updates
2026-04-22 banana pcb main v2
2026-04-23 PCB V2
2026-06-17 5.0X reset gates at startup
2026-06-17 add 5.0x to releases
2026-06-17 v3 test firmware for faster scan
2026-06-18 packing slip-

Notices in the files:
parts and their libraries:
tag-connect: ©2009 ROFA.cz - modified and updated by Robert Darlington ‹rdarlington@gmail.com›
